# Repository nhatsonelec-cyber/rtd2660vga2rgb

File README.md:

# RTD2660 VGA (header 12P) → LVDS 20P cho màn 7" 1024x600

Mạch điều khiển màn hình dùng chip Realtek **RTD2660**, thiết kế theo datasheet trong repo (`RTD2660.jsp.pdf`).

- **Đầu vào:** VGA trên **header 12 chân 2.54 mm**, cắm thẳng vào header VGA trên mainboard.
- **Đầu ra:** LVDS 1 kênh, 24 bit trên **đầu 20 chân 2.0 mm (J5)**, cùng **đầu đèn nền 4 chân 2.0 mm (J6)**.
  Hai đầu này khớp với cáp của màn 7" IPS 1024x600 LVDS 20 chân (Huadi).
- **Bản RGB 40P/50P tạm bỏ.** Mạch của chúng vẫn còn trong `tools/circuit.py` để làm sau.

| File | Nội dung |
|---|---|
| `eagle/RTD2660_VGA12P_LVDS.sch` | Sơ đồ nguyên lý, 4 trang |
| `eagle/RTD2660_VGA12P_LVDS.brd` | Board 120 x 80 mm, linh kiện đã đặt ở mặt trên, chưa đi dây |
| `eagle/rtd2660_board.lbr` | Thư viện linh kiện |
| `eagle/RTD2660_VGA12P_LVDS_BOM.csv` | Danh sách linh kiện |
| `preview/RTD2660_VGA12P_LVDS_preview.pdf` | Bản xem trước sơ đồ và board |
| `firmware/` | Script cấu hình firmware cho SDK RTD2660 |

## Trạng thái

- **Sơ đồ nguyên lý: xong.** Các net nối bằng nhãn tên.
- **Board: toàn bộ 114 linh kiện đặt ở mặt trên, chưa đi dây.** Có sẵn polygon GND ở mặt dưới.
- Mở bằng Eagle 7.x, 8.x hoặc 9.x. File `.brd` mở kèm và nhất quán với sơ đồ.
- **Đã kiểm tra:** KiCad đọc được file `.brd`, netlist khớp 100% từng pad với sơ đồ. DRC không có linh kiện chồng nhau.
  `tools/check_eagle.py` xác nhận mọi chân nằm trên lưới 0.1 inch.
- Khi đi dây, đi các cặp LVDS thành cặp vi sai 100 Ω, ngắn và bằng chiều dài. Thêm via tản nhiệt dưới pad GND của RTD2660.

## Sơ đồ chân các đầu nối

**J2 - VGA 1x12, 2.54 mm (đầu vào)**

| Chân | Tín hiệu |
|---|---|
| 1 | VGA_R |
| 2 | GND |
| 3 | VGA_G |
| 4 | GND |
| 5 | VGA_B |
| 6 | GND |
| 7 | VGA_HS |
| 8 | VGA_VS |
| 9 | GND |
| 10 | VGA_SDA |
| 11 | VGA_SCL |
| 12 | VGA_5V |

Chân 12 (+5V từ mainboard) không dùng. Nếu header VGA trên mainboard có thứ tự khác, sửa `VGA12_PINOUT` trong `tools/circuit.py`.

**J5 - LVDS 1x20, 2.0 mm (đầu đen của cáp màn)**

| Chân | Tín hiệu |
|---|---|
| 1 | VLCD |
| 2 | VLCD |
| 3 | PNL_LED_EN |
| 4 | GND |
| 5 | LVDS_E0- |
| 6 | LVDS_E0+ |
| 7 | GND |
| 8 | LVDS_E1- |
| 9 | LVDS_E1+ |
| 10 | GND |
| 11 | LVDS_E2- |
| 12 | LVDS_E2+ |
| 13 | GND |
| 14 | LVDS_EC- |
| 15 | LVDS_EC+ |
| 16 | GND |
| 17 | LVDS_E3- |
| 18 | LVDS_E3+ |
| 19 | không dùng |
| 20 | không dùng |

Chân 1-18 giống hệt sơ đồ chân của màn. Ở chế độ 1 kênh, RTD2660 xuất trên các cặp E (chân 86-95 của chip).

**J6 - đèn nền 1x4, 2.0 mm (đầu trắng của cáp màn)**

| Chân | Tín hiệu |
|---|---|
| 1 | +12V |
| 2 | PNL_LED_EN |
| 3 | PNL_BL_ADJ |
| 4 | GND |

**Thứ tự chân J6 là giả định.** Hãy đo cáp bằng đồng hồ: VLED nối chân 20 của màn, PWM nối chân 19, LED_EN nối chân 3.
Nếu khác, sửa `BL4_PINOUT` trong `tools/circuit.py` rồi chạy lại script.

- Chân độ sáng ra điện áp DC từ 0 đến 1.41 V, lấy từ PWM4 qua bộ lọc 10k / 7.5k / 1 µF. Màn nhận 0.7 đến 1.4 V.
- LED_EN lấy từ BL_ON qua 1k, có 10k kéo xuống.
- VLED lấy thẳng từ +12 V. Màn nhận 5 đến 12 V.

Các đầu nối khác:

- **J1, nguồn vào 12 V:** 1 = +12V, 2 = GND. Có cầu chì PTC 2 A và diode chống ngược.
- **J3, nạp firmware qua DDC:** GND, SDA, SCL.
- **J4, phím và IR (1x8):** 1 +3V3, 2 GND, 3 KEY_AD0, 4 KEY_AD1, 5 IR, 6 LED_G, 7 LED_R, 8 +5V.

## Nguồn

12 V → LM2596S-5.0 → 5 V. Từ 5 V có hai AMS1117-3.3: một cho phần số (PVCC, flash) và một cho phần analog (VDD, VADC).
Từ đó hai AMS1117-1.8 tạo VCCK (lõi) và ADC_VDD.
VDD 3.3 V của màn lấy từ một AMS1117-3.3 riêng, được bật bằng MOSFET AO3401A theo chân PANEL_ON.

## Bàn phím (J4)

SDK đọc phím bằng một kênh ADC 6 bit (KEY_AD0, chân 50). Trên board đã có điện trở kéo lên 10k.
Trên bo phím, mỗi nút nối KEY_AD0 xuống GND qua một điện trở:

| Nút | Điện trở xuống GND | Mã ADC |
|---|---|---|
| POWER | 0 Ω | 0 |
| MENU | 1.8k | 10 |
| RIGHT | 3.9k | 18 |
| LEFT | 8.2k | 28 |
| SOURCE | 22k | 43 |

## Gán chân GPIO

| Chân | Chức năng chip | Net | Dùng cho |
|---|---|---|---|
| 50 | P6.0 / A-ADC0 | KEY_AD0 | Keypad resistor ladder 1 (ADC) |
| 51 | P6.1 / A-ADC1 | KEY_AD1 | Keypad resistor ladder 2 (ADC) |
| 52 | P6.2 | LED_R_DRV | Red / standby LED, active high |
| 53 | P6.3 | LED_G_DRV | Green / power LED, active high |
| 58 | DDCSCL1 (P3.0) | DDC_SCL | VGA DDC clock, ISP programming |
| 59 | DDCSDA1 (P3.1) | DDC_SDA | VGA DDC data, ISP programming |
| 98 | P5.4 | PANEL_ON | Panel power enable, active high |
| 99 | P5.5 | BL_ON | Backlight enable, active high |
| 100 | P5.6 / PWM4 | BL_PWM | Backlight brightness PWM, high = bright |
| 113 | P3.6 / IrDA | IR_IN | IR receiver input |

## Firmware

RTD2660 cần firmware trong flash W25Q40. Xem `firmware/README.md`.
Script áp cấu hình board và màn 1024x600 lên SDK RTD2660, sau đó biên dịch bằng Keil C51.

## Những điểm cần kiểm tra

1. **Thạch anh 27 MHz**, giống board tham chiếu PCB800099 của SDK.
2. **Chân SPI flash.** Tên chân (115 SCLK, 116 SI, 117 SO) và phần mô tả trong datasheet lệch nhau ở chân 115/116.
   Mạch theo tên chân. Có sẵn cặp điện trở 33R (không hàn) để đảo CLK/DI nếu flash không chạy.
3. **Thứ tự chân header VGA 12P và đầu đèn nền 4 chân.** Phải khớp với mainboard và cáp màn.
4. **Timing màn** (tổng 1344 x 635, 51.2 MHz) là giá trị phổ biến của màn 7" 1024x600. Nếu có datasheet màn, đối chiếu lại.

## Sửa thiết kế

```bash
pip install lxml matplotlib
python3 tools/gen_eagle.py      # sinh file Eagle và BOM
python3 tools/check_eagle.py    # kiểm tra
python3 tools/preview.py        # sinh bản xem trước PDF
```

- `tools/circuit.py`: mạch điện, sơ đồ chân các đầu nối, bảng GPIO
- `tools/parts.py`: ký hiệu, footprint, sơ đồ chân RTD2660
- `tools/gen_eagle.py`: ghi file Eagle và đặt linh kiện trên board
- `firmware/apply_board.py`: áp cấu hình board và màn lên SDK firmware RTD2660

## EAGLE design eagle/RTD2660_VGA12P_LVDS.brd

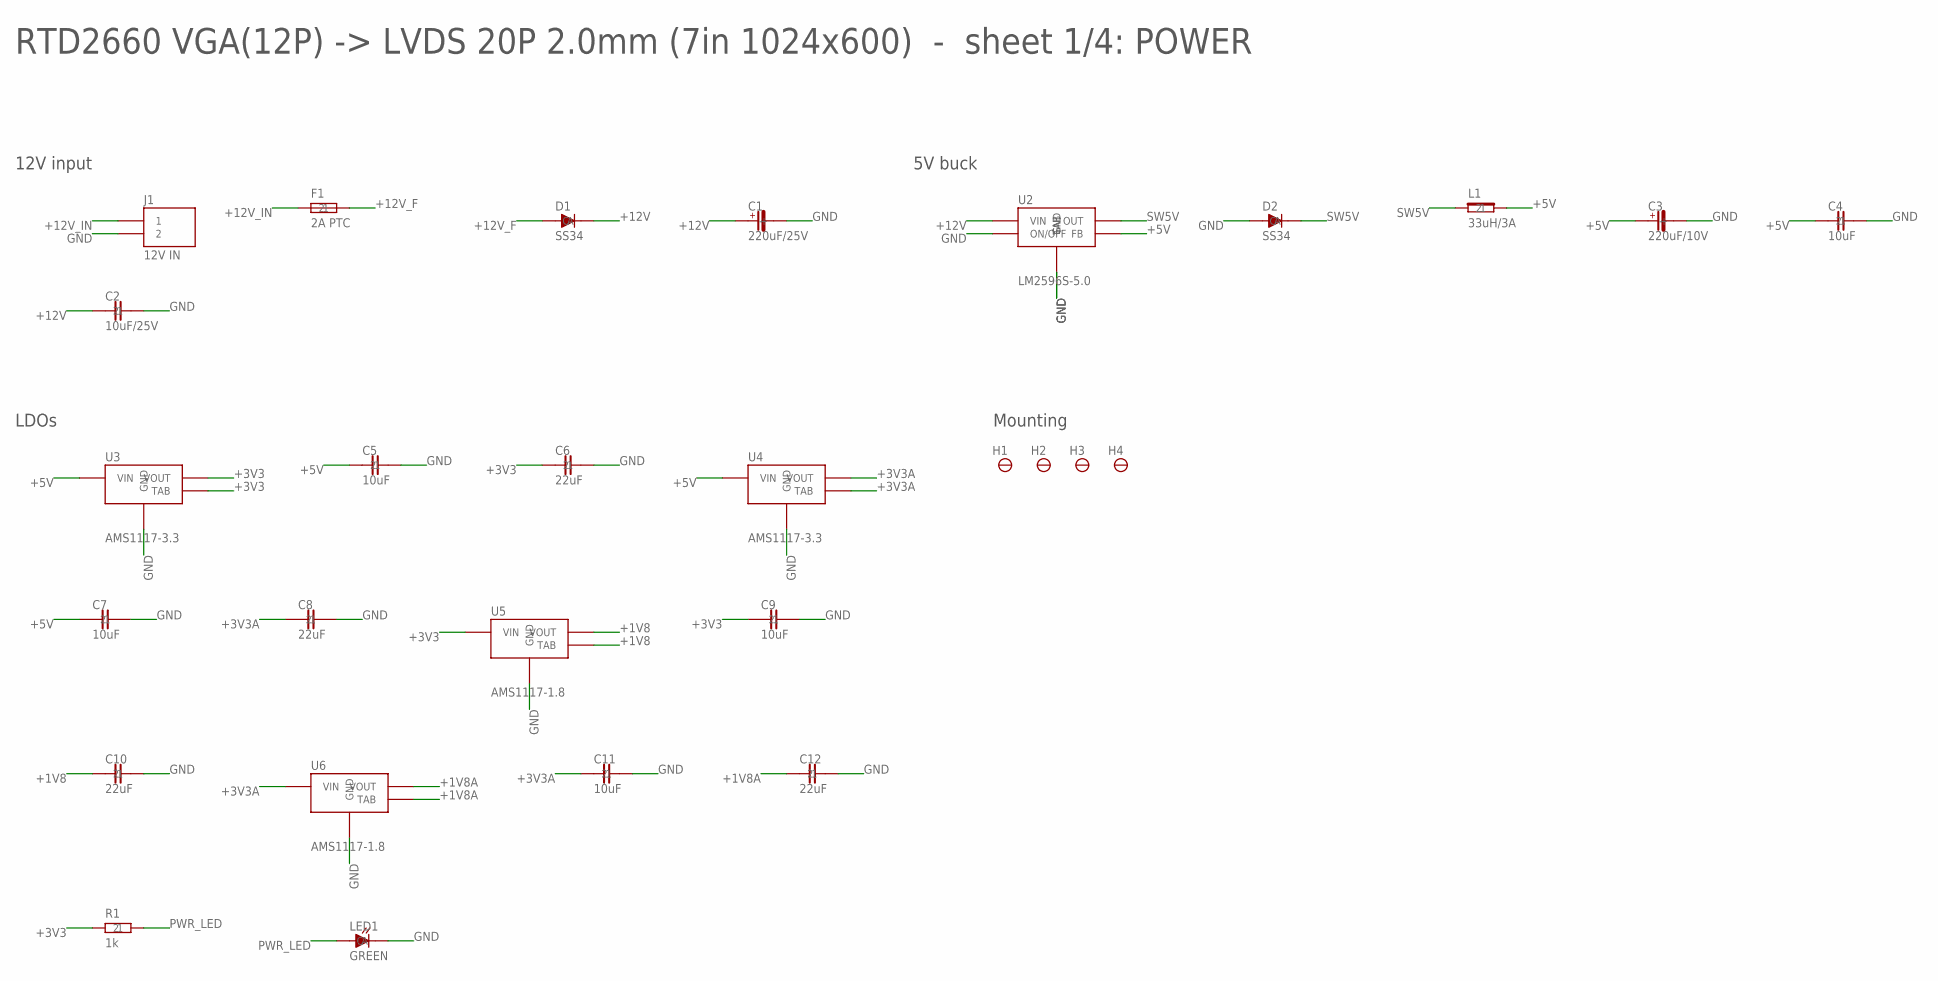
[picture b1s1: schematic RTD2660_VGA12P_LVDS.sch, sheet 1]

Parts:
C1: 220uF/25V; CPOL-D8
C2: 10uF/25V; 1206
C3: 220uF/10V; CPOL-D8
C4, C5, C7, C9, C11: 10uF; 0805
C6, C8, C10, C12: 22uF; 1206
D1, D2: SS34; SMA
F1: 2A PTC; 1206
H1, H2, H3, H4: M3; HOLE3.2
J1: 12V IN; HDR1X2-2.54
L1: 33uH/3A; IND-12X12
LED1: GREEN; LED0603
R1: 1k; 0603
U2: LM2596S-5.0; TO263-5
U3, U4: AMS1117-3.3; SOT223
U5, U6: AMS1117-1.8; SOT223

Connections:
+1V8: C10.1, U5.2 (VOUT), U5.4 (TAB); also elsewhere on the board
+1V8A: C12.1, U6.2 (VOUT), U6.4 (TAB); also elsewhere on the board
+3V3: C6.1, C9.1, R1.1, U3.2 (VOUT), U3.4 (TAB), U5.3 (VIN); also elsewhere on the board
+3V3A: C8.1, C11.1, U4.2 (VOUT), U4.4 (TAB), U6.3 (VIN); also elsewhere on the board
+5V: C3.+, C4.1, C5.1, C7.1, L1.2, U2.4 (FB), U3.3 (VIN), U4.3 (VIN); also elsewhere on the board
+12V: C1.+, C2.1, D1.C, U2.1 (VIN); also elsewhere on the board
+12V_F: D1.A, F1.2
+12V_IN: F1.1, J1.1
GND: C1.-, C2.2, C3.-, C4.2, C5.2, C6.2, C7.2, C8.2, C9.2, C10.2, C11.2, C12.2, D2.A, J1.2, LED1.C, U2.3 (GND), U2.5 (ON/OFF), U2.6 (TAB), U3.1 (GND), U4.1 (GND), U5.1 (GND), U6.1 (GND); also elsewhere on the board
PWR_LED: LED1.A, R1.2
SW5V: D2.C, L1.1, U2.2 (OUT)

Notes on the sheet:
RTD2660 VGA(12P) -> LVDS 20P 2.0mm (7in 1024x600) - sheet 1/4: POWER
12V input
5V buck
LDOs
Mounting

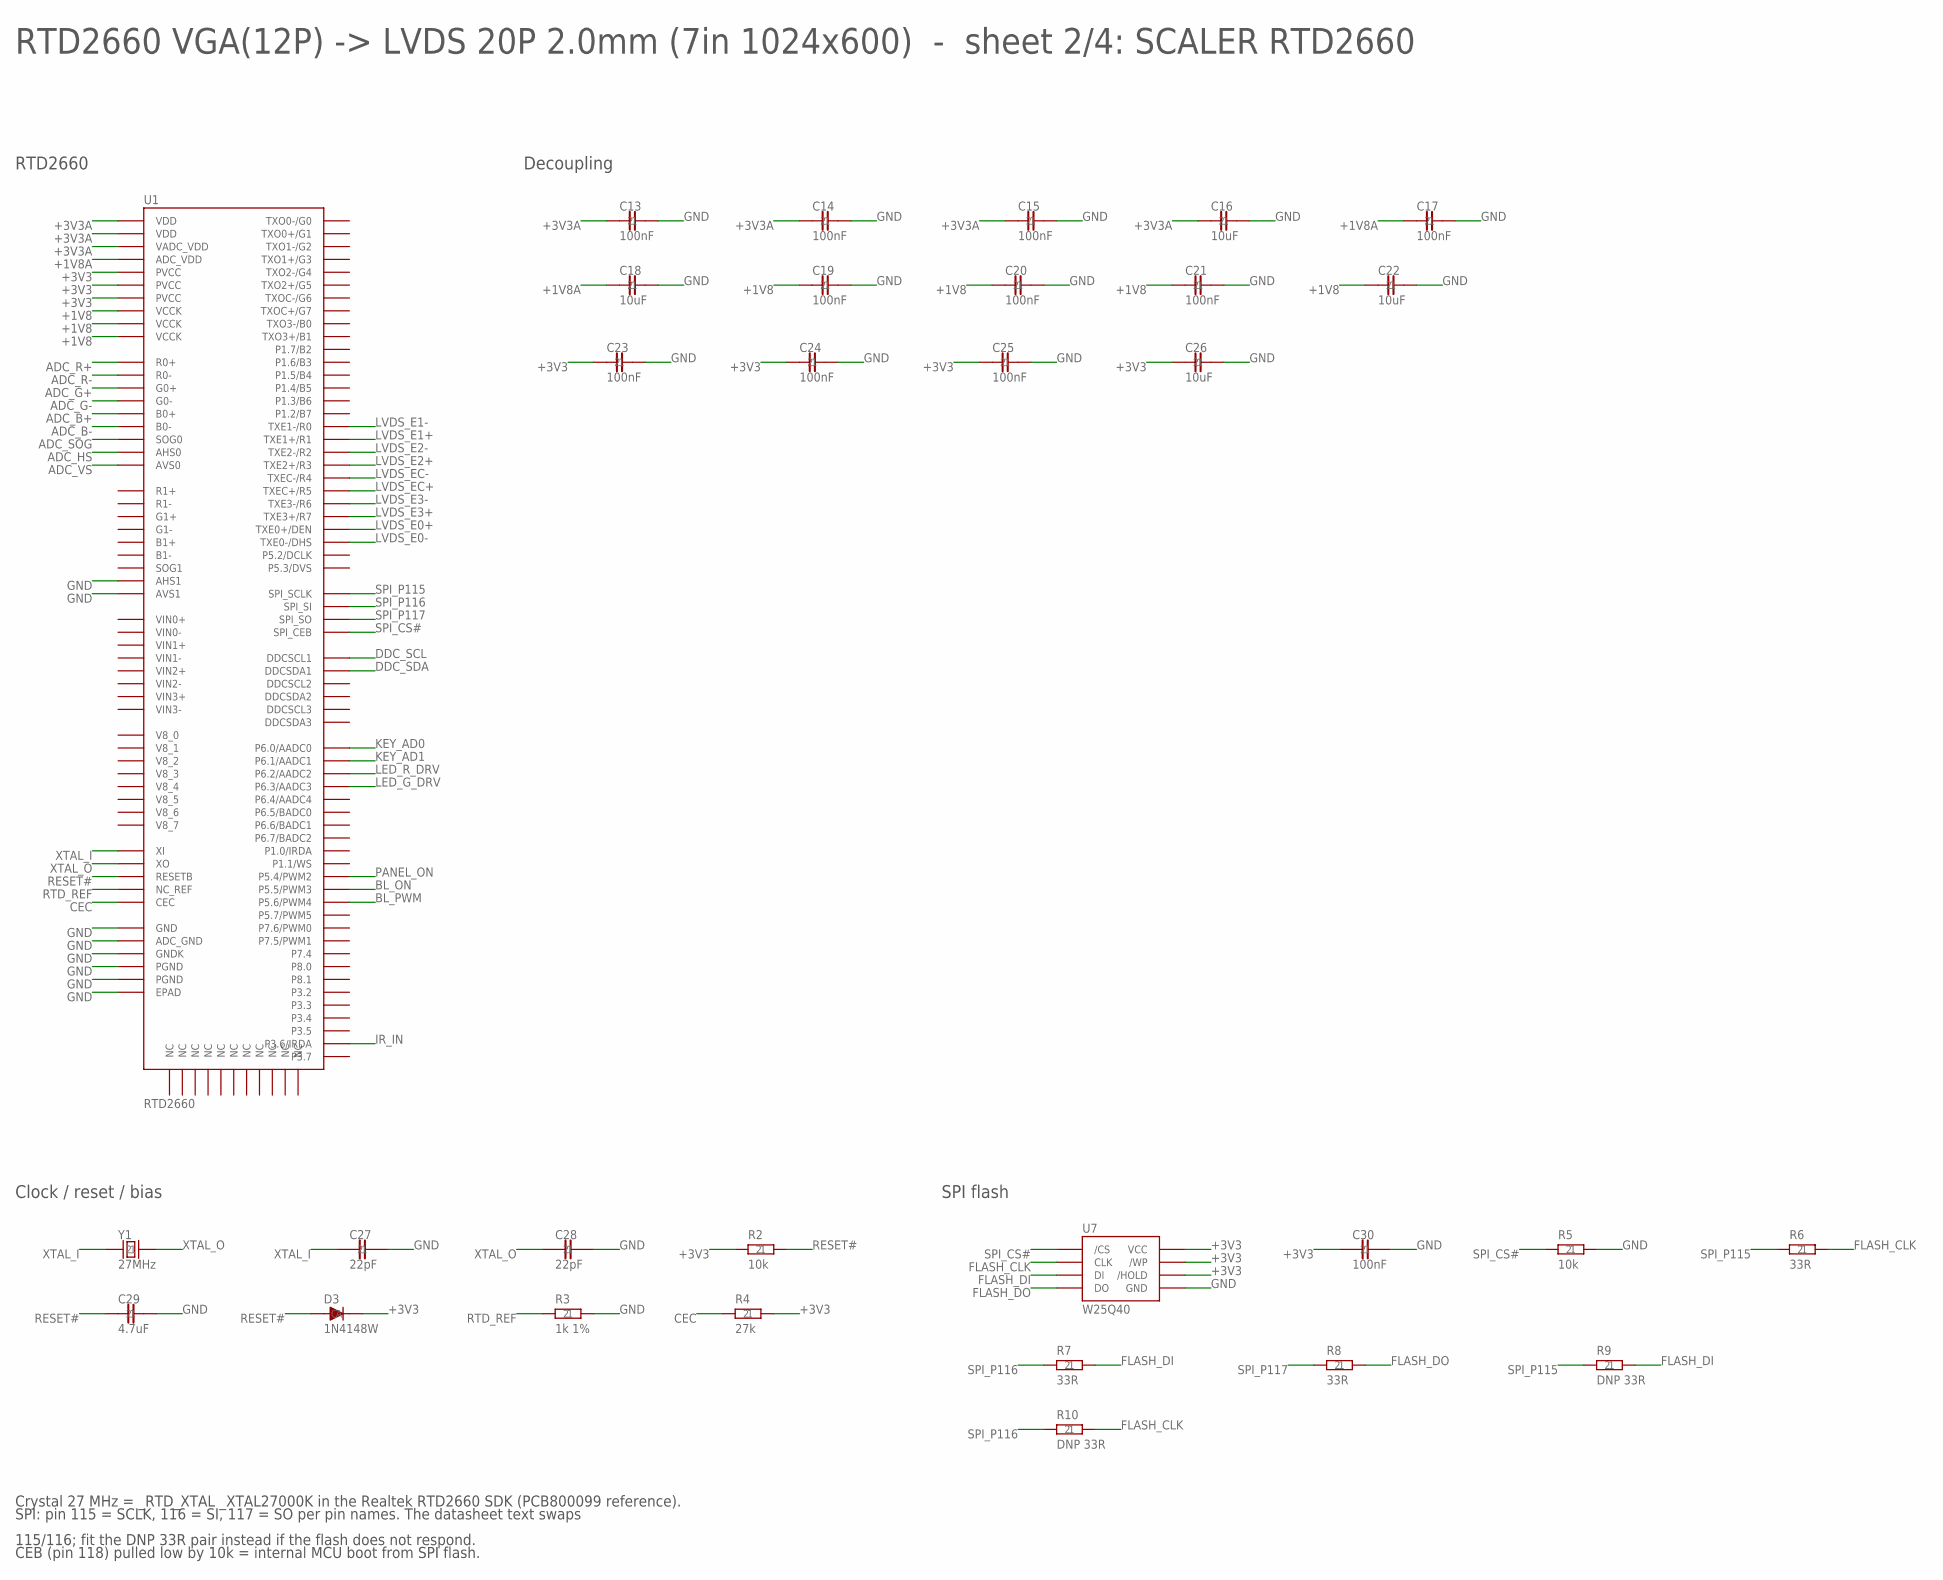
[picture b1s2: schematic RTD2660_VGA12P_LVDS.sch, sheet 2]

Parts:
C13, C14, C15, C17, C19, C20, C21, C23, C24, C25, C30: 100nF; 0603
C16, C18, C22, C26: 10uF; 0805
C27, C28: 22pF; 0603
C29: 4.7uF; 0805
D3: 1N4148W; SOD123
R2, R5: 10k; 0603
R3: 1k 1%; 0603
R4: 27k; 0603
R6, R7, R8: 33R; 0603
R9, R10: DNP 33R; 0603
U1: RTD2660; LQFP128-14X20-EP
U7: W25Q40; SOIC8
Y1: 27MHz; HC49SMD

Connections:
+1V8: C19.1, C20.1, C21.1, C22.1, U1.60 (VCCK), U1.73 (VCCK), U1.120 (VCCK); also elsewhere on the board
+1V8A: C17.1, C18.1, U1.23 (ADC_VDD); also elsewhere on the board
+3V3: C23.1, C24.1, C25.1, C26.1, C30.1, D3.C, R2.1, R4.2, U1.62 (PVCC), U1.84 (PVCC), U1.106 (PVCC), U7.3 (/WP), U7.7 (/HOLD), U7.8 (VCC); also elsewhere on the board
+3V3A: C13.1, C14.1, C15.1, C16.1, U1.1 (VDD), U1.20 (VDD), U1.49 (VADC_VDD); also elsewhere on the board
ADC_B+: U1.25 (B0+); also elsewhere on the board
ADC_B-: U1.24 (B0-); also elsewhere on the board
ADC_G+: U1.27 (G0+); also elsewhere on the board
ADC_G-: U1.26 (G0-); also elsewhere on the board
ADC_HS: U1.22 (AHS0); also elsewhere on the board
ADC_R+: U1.30 (R0+); also elsewhere on the board
ADC_R-: U1.29 (R0-); also elsewhere on the board
ADC_SOG: U1.28 (SOG0); also elsewhere on the board
ADC_VS: U1.21 (AVS0); also elsewhere on the board
BL_ON: U1.99 (P5.5/PWM3); also elsewhere on the board
BL_PWM: U1.100 (P5.6/PWM4); also elsewhere on the board
CEC: R4.1, U1.126 (CEC)
DDC_SCL: U1.58 (DDCSCL1); also elsewhere on the board
DDC_SDA: U1.59 (DDCSDA1); also elsewhere on the board
FLASH_CLK: R6.2, R10.2, U7.6 (CLK)
FLASH_DI: R7.2, R9.2, U7.5 (DI)
FLASH_DO: R8.2, U7.2 (DO)
GND: C13.2, C14.2, C15.2, C16.2, C17.2, C18.2, C19.2, C20.2, C21.2, C22.2, C23.2, C24.2, C25.2, C26.2, C27.2, C28.2, C29.2, C30.2, R3.2, R5.2, U1.11 (GND), U1.38 (ADC_GND), U1.39 (AHS1), U1.40 (AVS1), U1.61 (GNDK), U1.85 (PGND), U1.107 (PGND), U1.EP (EPAD), U7.4 (GND); also elsewhere on the board
IR_IN: U1.113 (P3.6/IRDA); also elsewhere on the board
KEY_AD0: U1.50 (P6.0/AADC0); also elsewhere on the board
KEY_AD1: U1.51 (P6.1/AADC1); also elsewhere on the board
LED_G_DRV: U1.53 (P6.3/AADC3); also elsewhere on the board
LED_R_DRV: U1.52 (P6.2/AADC2); also elsewhere on the board
LVDS_E0+: U1.94 (TXE0+/DEN); also elsewhere on the board
LVDS_E0-: U1.95 (TXE0-/DHS); also elsewhere on the board
LVDS_E1+: U1.92 (TXE1+/R1); also elsewhere on the board
LVDS_E1-: U1.93 (TXE1-/R0); also elsewhere on the board
LVDS_E2+: U1.90 (TXE2+/R3); also elsewhere on the board
LVDS_E2-: U1.91 (TXE2-/R2); also elsewhere on the board
LVDS_E3+: U1.86 (TXE3+/R7); also elsewhere on the board
LVDS_E3-: U1.87 (TXE3-/R6); also elsewhere on the board
LVDS_EC+: U1.88 (TXEC+/R5); also elsewhere on the board
LVDS_EC-: U1.89 (TXEC-/R4); also elsewhere on the board
PANEL_ON: U1.98 (P5.4/PWM2); also elsewhere on the board
RESET#: C29.1, D3.A, R2.2, U1.125 (RESETB)
RTD_REF: R3.1, U1.2 (NC_REF)
SPI_CS#: R5.1, U1.118 (SPI_CEB), U7.1 (/CS)
SPI_P115: R6.1, R9.1, U1.115 (SPI_SCLK)
SPI_P116: R7.1, R10.1, U1.116 (SPI_SI)
SPI_P117: R8.1, U1.117 (SPI_SO)
XTAL_I: C27.1, U1.128 (XI), Y1.1
XTAL_O: C28.1, U1.127 (XO), Y1.2

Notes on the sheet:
RTD2660 VGA(12P) -> LVDS 20P 2.0mm (7in 1024x600) - sheet 2/4: SCALER RTD2660
RTD2660
Decoupling
Clock / reset / bias
SPI flash
Crystal 27 MHz = _RTD_XTAL _XTAL27000K in the Realtek RTD2660 SDK (PCB800099 reference).
SPI: pin 115 = SCLK, 116 = SI, 117 = SO per pin names. The datasheet text swaps
115/116; fit the DNP 33R pair instead if the flash does not respond.
CEB (pin 118) pulled low by 10k = internal MCU boot from SPI flash.

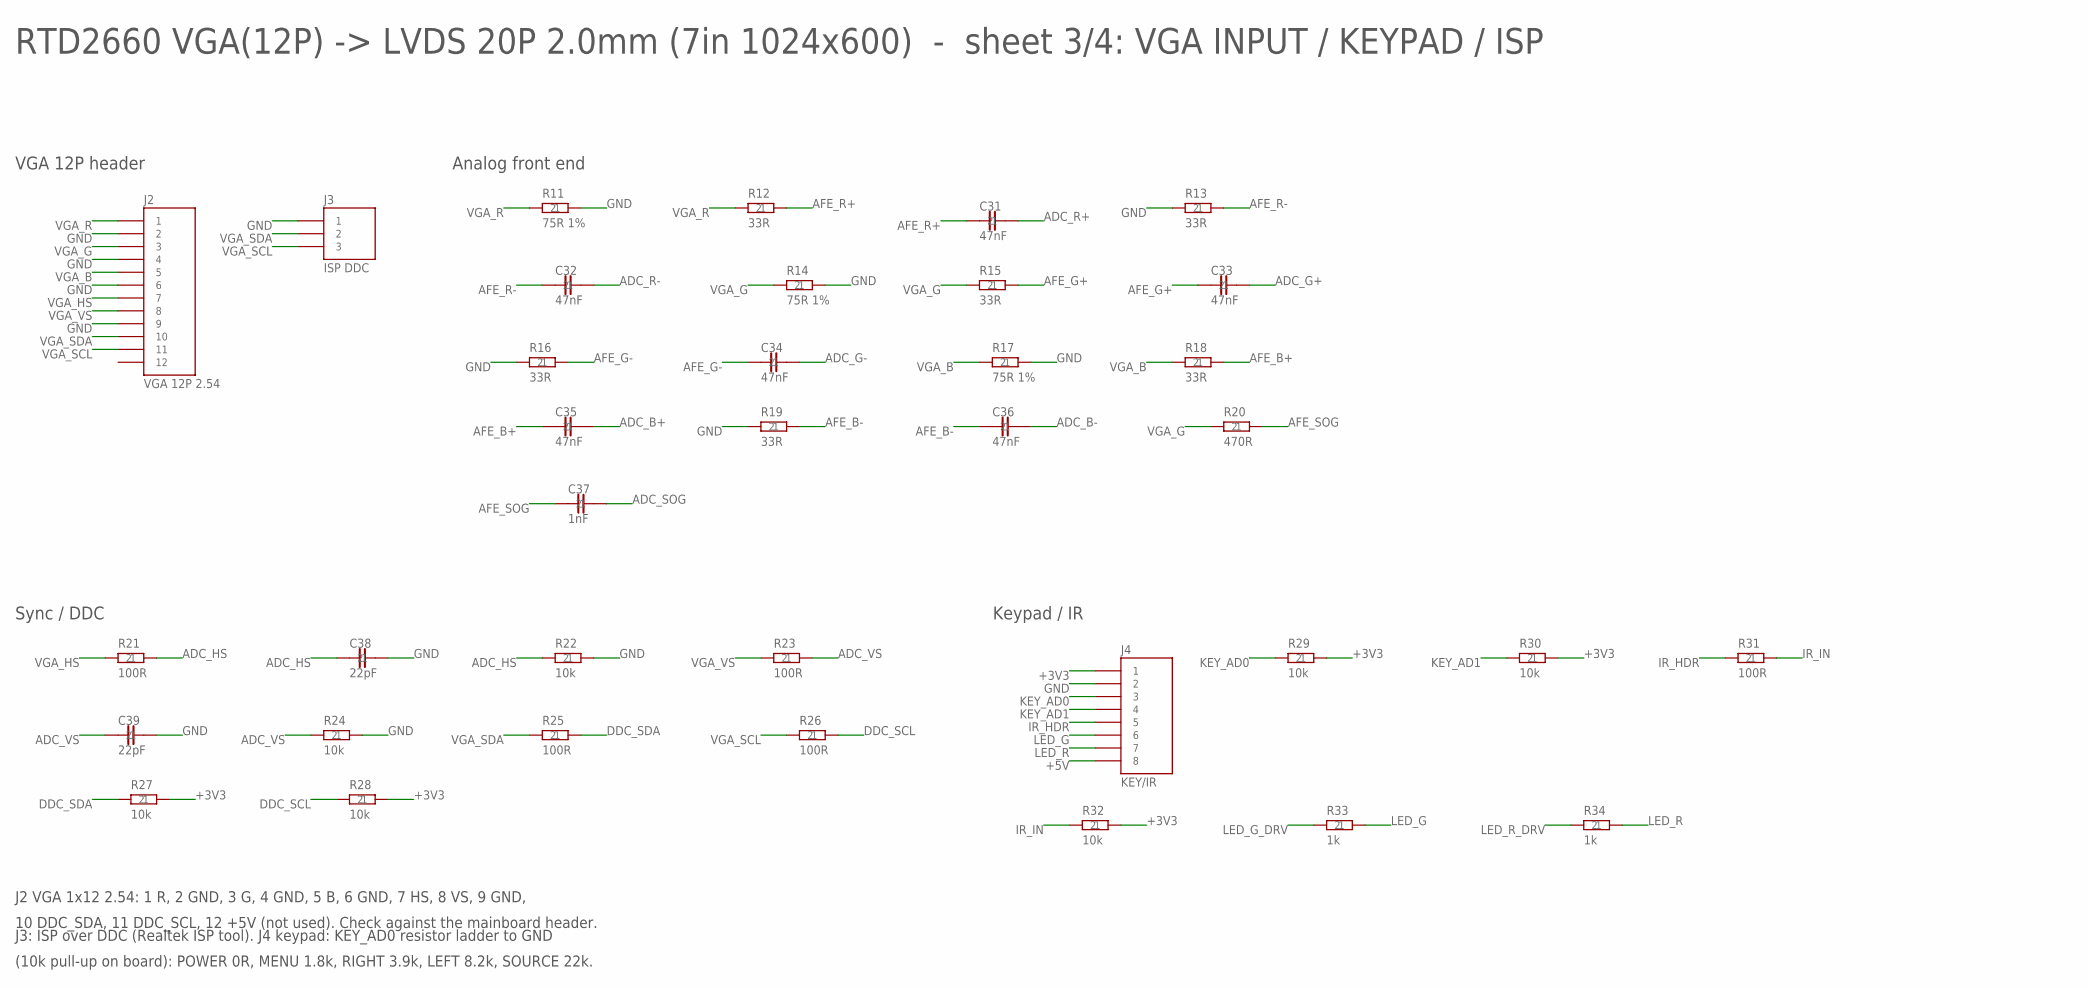
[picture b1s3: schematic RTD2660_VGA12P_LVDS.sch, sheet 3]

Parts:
C31, C32, C33, C34, C35, C36: 47nF; 0603
C37: 1nF; 0603
C38, C39: 22pF; 0603
J2: VGA 12P 2.54; HDR1X12-2.54
J3: ISP DDC; HDR1X3-2.54
J4: KEY/IR; HDR1X8-2.54
R11, R14, R17: 75R 1%; 0603
R12, R13, R15, R16, R18, R19: 33R; 0603
R20: 470R; 0603
R21, R23, R25, R26, R31: 100R; 0603
R22, R24, R27, R28, R29, R30, R32: 10k; 0603
R33, R34: 1k; 0603

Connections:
+3V3: J4.1, R27.2, R28.2, R29.2, R30.2, R32.2; also elsewhere on the board
+5V: J4.8; also elsewhere on the board
ADC_B+: C35.2; also elsewhere on the board
ADC_B-: C36.2; also elsewhere on the board
ADC_G+: C33.2; also elsewhere on the board
ADC_G-: C34.2; also elsewhere on the board
ADC_HS: C38.1, R21.2, R22.1; also elsewhere on the board
ADC_R+: C31.2; also elsewhere on the board
ADC_R-: C32.2; also elsewhere on the board
ADC_SOG: C37.2; also elsewhere on the board
ADC_VS: C39.1, R23.2, R24.1; also elsewhere on the board
AFE_B+: C35.1, R18.2
AFE_B-: C36.1, R19.2
AFE_G+: C33.1, R15.2
AFE_G-: C34.1, R16.2
AFE_R+: C31.1, R12.2
AFE_R-: C32.1, R13.2
AFE_SOG: C37.1, R20.2
DDC_SCL: R26.2, R28.1; also elsewhere on the board
DDC_SDA: R25.2, R27.1; also elsewhere on the board
GND: C38.2, C39.2, J2.2, J2.4, J2.6, J2.9, J3.1, J4.2, R11.2, R13.1, R14.2, R16.1, R17.2, R19.1, R22.2, R24.2; also elsewhere on the board
IR_HDR: J4.5, R31.1
IR_IN: R31.2, R32.1; also elsewhere on the board
KEY_AD0: J4.3, R29.1; also elsewhere on the board
KEY_AD1: J4.4, R30.1; also elsewhere on the board
LED_G: J4.6, R33.2
LED_G_DRV: R33.1; also elsewhere on the board
LED_R: J4.7, R34.2
LED_R_DRV: R34.1; also elsewhere on the board
VGA_B: J2.5, R17.1, R18.1
VGA_G: J2.3, R14.1, R15.1, R20.1
VGA_HS: J2.7, R21.1
VGA_R: J2.1, R11.1, R12.1
VGA_SCL: J2.11, J3.3, R26.1
VGA_SDA: J2.10, J3.2, R25.1
VGA_VS: J2.8, R23.1

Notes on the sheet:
RTD2660 VGA(12P) -> LVDS 20P 2.0mm (7in 1024x600) - sheet 3/4: VGA INPUT / KEYPAD / ISP
VGA 12P header
Analog front end
Sync / DDC
Keypad / IR
J2 VGA 1x12 2.54: 1 R, 2 GND, 3 G, 4 GND, 5 B, 6 GND, 7 HS, 8 VS, 9 GND,
10 DDC_SDA, 11 DDC_SCL, 12 +5V (not used). Check against the mainboard header.
J3: ISP over DDC (Realtek ISP tool). J4 keypad: KEY_AD0 resistor ladder to GND
(10k pull-up on board): POWER 0R, MENU 1.8k, RIGHT 3.9k, LEFT 8.2k, SOURCE 22k.

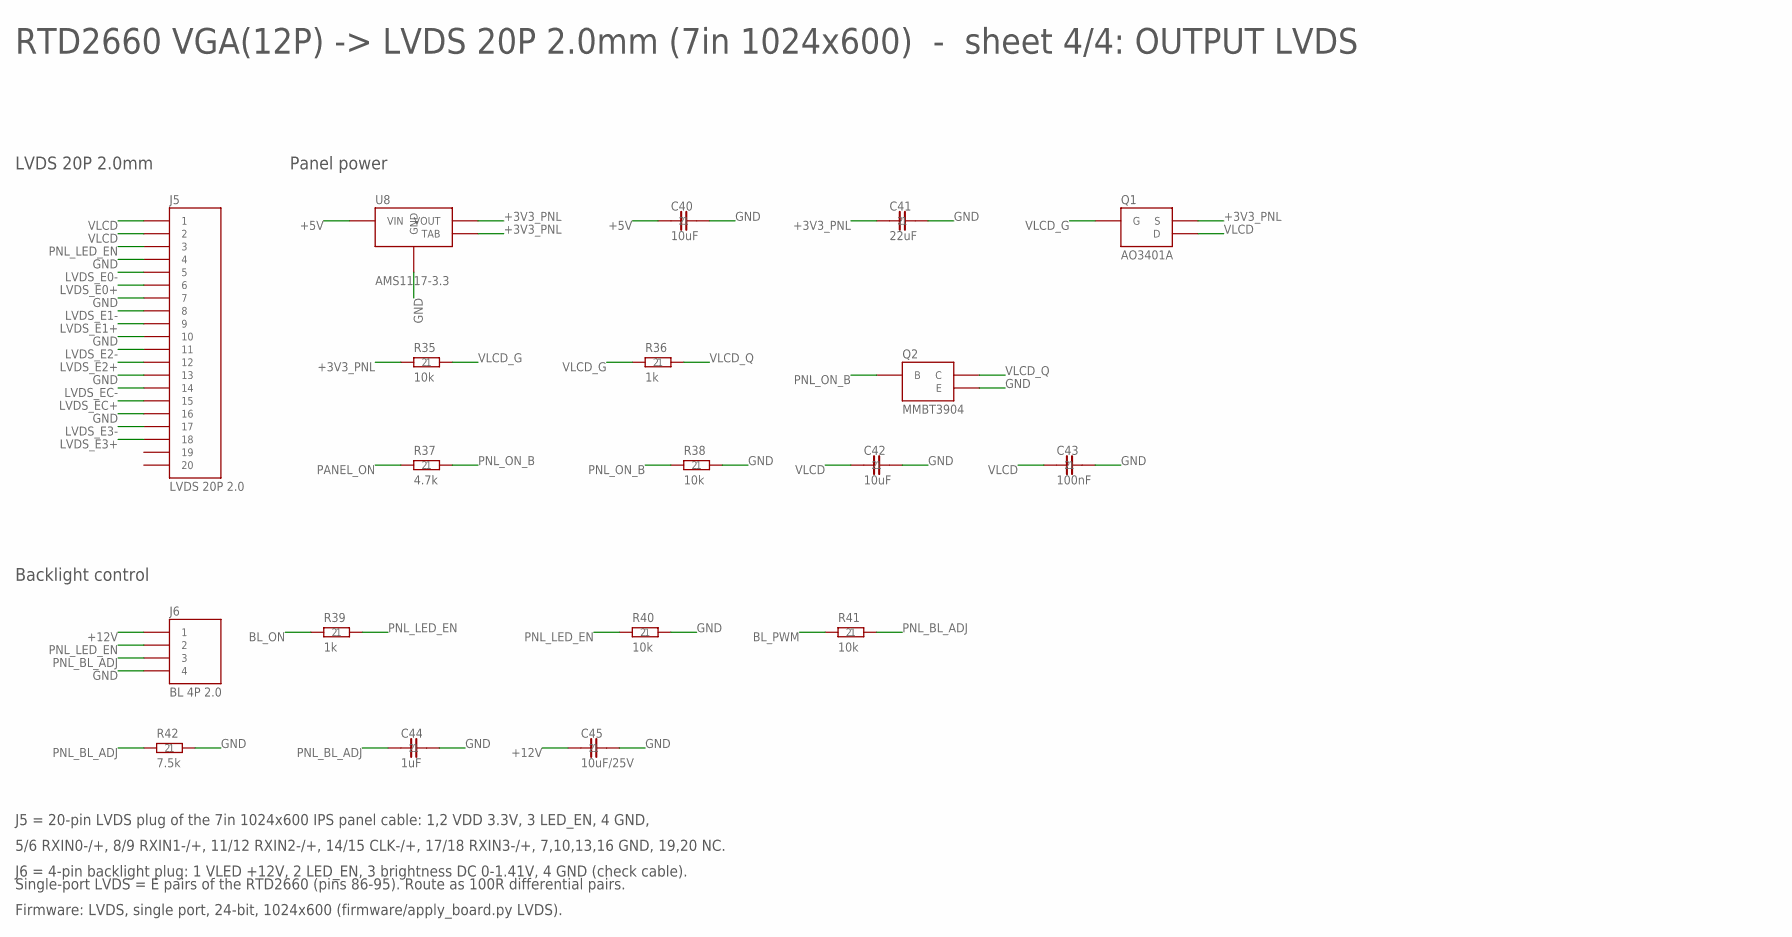
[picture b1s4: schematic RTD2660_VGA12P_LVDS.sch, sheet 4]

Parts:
C40, C42: 10uF; 0805
C41: 22uF; 1206
C43: 100nF; 0603
C44: 1uF; 0603
C45: 10uF/25V; 1206
J5: LVDS 20P 2.0; HDR1X20-2.0
J6: BL 4P 2.0; HDR1X4-2.0
Q1: AO3401A; SOT23
Q2: MMBT3904; SOT23
R35, R38, R40, R41: 10k; 0603
R36, R39: 1k; 0603
R37: 4.7k; 0603
R42: 7.5k; 0603
U8: AMS1117-3.3; SOT223

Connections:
+3V3_PNL: C41.1, Q1.2 (S), R35.1, U8.2 (VOUT), U8.4 (TAB)
+5V: C40.1, U8.3 (VIN); also elsewhere on the board
+12V: C45.1, J6.1; also elsewhere on the board
BL_ON: R39.1; also elsewhere on the board
BL_PWM: R41.1; also elsewhere on the board
GND: C40.2, C41.2, C42.2, C43.2, C44.2, C45.2, J5.4, J5.7, J5.10, J5.13, J5.16, J6.4, Q2.2 (E), R38.2, R40.2, R42.2, U8.1 (GND); also elsewhere on the board
LVDS_E0+: J5.6; also elsewhere on the board
LVDS_E0-: J5.5; also elsewhere on the board
LVDS_E1+: J5.9; also elsewhere on the board
LVDS_E1-: J5.8; also elsewhere on the board
LVDS_E2+: J5.12; also elsewhere on the board
LVDS_E2-: J5.11; also elsewhere on the board
LVDS_E3+: J5.18; also elsewhere on the board
LVDS_E3-: J5.17; also elsewhere on the board
LVDS_EC+: J5.15; also elsewhere on the board
LVDS_EC-: J5.14; also elsewhere on the board
PANEL_ON: R37.1; also elsewhere on the board
PNL_BL_ADJ: C44.1, J6.3, R41.2, R42.1
PNL_LED_EN: J5.3, J6.2, R39.2, R40.1
PNL_ON_B: Q2.1 (B), R37.2, R38.1
VLCD: C42.1, C43.1, J5.1, J5.2, Q1.3 (D)
VLCD_G: Q1.1 (G), R35.2, R36.1
VLCD_Q: Q2.3 (C), R36.2

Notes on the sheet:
RTD2660 VGA(12P) -> LVDS 20P 2.0mm (7in 1024x600) - sheet 4/4: OUTPUT LVDS
LVDS 20P 2.0mm
Panel power
Backlight control
J5 = 20-pin LVDS plug of the 7in 1024x600 IPS panel cable: 1,2 VDD 3.3V, 3 LED_EN, 4 GND,
5/6 RXIN0-/+, 8/9 RXIN1-/+, 11/12 RXIN2-/+, 14/15 CLK-/+, 17/18 RXIN3-/+, 7,10,13,16 GND, 19,20 NC.
J6 = 4-pin backlight plug: 1 VLED +12V, 2 LED_EN, 3 brightness DC 0-1.41V, 4 GND (check cable).
Single-port LVDS = E pairs of the RTD2660 (pins 86-95). Route as 100R differential pairs.
Firmware: LVDS, single port, 24-bit, 1024x600 (firmware/apply_board.py LVDS).

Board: 1 copper layer, 114 parts (0 on the bottom side), 76 nets, no tracks yet.

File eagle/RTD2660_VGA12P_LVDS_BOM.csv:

Qty,Value,Package,Description,Fit,References
1,220uF/25V,CPOL-D8,"Electrolytic capacitor, radial D8",yes,C1
2,10uF/25V,1206,Ceramic capacitor 1206,yes,C2 C45
1,220uF/10V,CPOL-D8,"Electrolytic capacitor, radial D8",yes,C3
11,10uF,0805,Ceramic capacitor 0805,yes,C4 C5 C7 C9 C11 C16 C18 C22 C26 C40 C42
5,22uF,1206,Ceramic capacitor 1206,yes,C6 C8 C10 C12 C41
12,100nF,0603,Ceramic capacitor 0603,yes,C13 C14 C15 C17 C19 C20 C21 C23 C24 C25 C30 C43
4,22pF,0603,Ceramic capacitor 0603,yes,C27 C28 C38 C39
1,4.7uF,0805,Ceramic capacitor 0805,yes,C29
6,47nF,0603,Ceramic capacitor 0603,yes,C31 C32 C33 C34 C35 C36
1,1nF,0603,Ceramic capacitor 0603,yes,C37
1,1uF,0603,Ceramic capacitor 0603,yes,C44
2,SS34,SMA,Schottky diode SMA (SS34),yes,D1 D2
1,1N4148W,SOD123,Diode SOD-123,yes,D3
1,2A PTC,1206,Resettable fuse 1206,yes,F1
1,12V IN,HDR1X2-2.54,1 x 2 pin header 2.54 mm,yes,J1
1,VGA 12P 2.54,HDR1X12-2.54,1 x 12 pin header 2.54 mm,yes,J2
1,ISP DDC,HDR1X3-2.54,1 x 3 pin header 2.54 mm,yes,J3
1,KEY/IR,HDR1X8-2.54,1 x 8 pin header 2.54 mm,yes,J4
1,LVDS 20P 2.0,HDR1X20-2.0,"1 x 20 pin header 2.0 mm, LVDS panel connector",yes,J5
1,BL 4P 2.0,HDR1X4-2.0,"1 x 4 pin header 2.0 mm, backlight",yes,J6
1,33uH/3A,IND-12X12,Power inductor 12 x 12 mm,yes,L1
1,GREEN,LED0603,LED 0603,yes,LED1
1,AO3401A,SOT23,P-channel MOSFET SOT-23 (AO3401A / AO3407A),yes,Q1
1,MMBT3904,SOT23,NPN transistor SOT-23 (MMBT3904),yes,Q2
5,1k,0603,Resistor 0603,yes,R1 R33 R34 R36 R39
13,10k,0603,Resistor 0603,yes,R2 R5 R22 R24 R27 R28 R29 R30 R32 R35 R38 R40 R41
1,1k 1%,0603,Resistor 0603,yes,R3
1,27k,0603,Resistor 0603,yes,R4
9,33R,0603,Resistor 0603,yes,R6 R7 R8 R12 R13 R15 R16 R18 R19
2,33R,0603,Resistor 0603,DNP,R9 R10
3,75R 1%,0603,Resistor 0603,yes,R11 R14 R17
1,470R,0603,Resistor 0603,yes,R20
5,100R,0603,Resistor 0603,yes,R21 R23 R25 R26 R31
1,4.7k,0603,Resistor 0603,yes,R37
1,7.5k,0603,Resistor 0603,yes,R42
1,RTD2660,LQFP128-14X20-EP,"Realtek RTD2660 flat panel display controller, 128-pin E-PAD LQFP 14 x 20 mm",yes,U1
1,LM2596S-5.0,TO263-5,"LM2596S buck regulator, TO-263-5 (tab = GND)",yes,U2
3,AMS1117-3.3,SOT223,"AMS1117 LDO, SOT-223 (tab = VOUT)",yes,U3 U4 U8
2,AMS1117-1.8,SOT223,"AMS1117 LDO, SOT-223 (tab = VOUT)",yes,U5 U6
1,W25Q40,SOIC8,"SPI NOR flash 25-series, SOIC-8 (W25Q40 / MX25L4006)",yes,U7
1,27MHz,HC49SMD,Crystal HC-49/US SMD,yes,Y1

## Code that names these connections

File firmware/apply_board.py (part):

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
# --------------------------------------------------------------------- board (all variants)
# GPIO map of this board (see README.md):
#   pin 50  P6.0/ADCA0  KEY_AD0 (keypad ladder)   pin 51 P6.1/ADCA1 KEY_AD1 (spare)
#   pin 52  P6.2        LED red  (bLED1)          pin 53 P6.3       LED green (bLED2)
#   pin 98  P5.4        PANEL_ON, active high     pin 99 P5.5       BL_ON, active high
#   pin 100 PWM4        BL_PWM                    pin 113 IrDA      IR receiver
#   pin 58/59 DDC1      VGA DDC / ISP             crystal 27 MHz
PCB_DEFINES = {
    "_RTD_XTAL": "_XTAL27000K",
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    "_PIN_58_59_DDC1_ENABLE": "(1 & 0x01)",
    "_PIN_96": "(4 & 0x07)",          # DCLK
    "_PIN_97": "(4 & 0x07)",          # DVS
    "_PIN_98": "(2 & 0x03)",          # P5.4   PANEL_ON, push-pull
    "_PIN_99": "(2 & 0x07)",          # P5.5   BL_ON, push-pull
    "_PIN_100": "(3 & 0x07)",         # PWM4   backlight
    "_PIN_113": "(6 & 0x07)",         # IrDA
    "bPANELPOWER": "(_MCU_PORT54)",
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
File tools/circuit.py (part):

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
# 1 x 4 pin 2.0 mm backlight connector (white 4-pin plug of the panel cable).
# Order is an assumption: check the cable with a multimeter (VLED / EN / PWM / GND).
BL4_PINOUT = {1: "+12V", 2: "PNL_LED_EN", 3: "PNL_BL_ADJ", 4: "GND"}

# 40-pin TTL RGB (AT043TN24 / 4.3"-7" 40P standard pinout)
RGB40_PINOUT = {1: "LED_K", 2: "LED_A", 3: "GND", 4: "VLCD"}
for i in range(8):
    RGB40_PINOUT[5 + i] = "TTL_R%d" % i
    RGB40_PINOUT[13 + i] = "TTL_G%d" % i
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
